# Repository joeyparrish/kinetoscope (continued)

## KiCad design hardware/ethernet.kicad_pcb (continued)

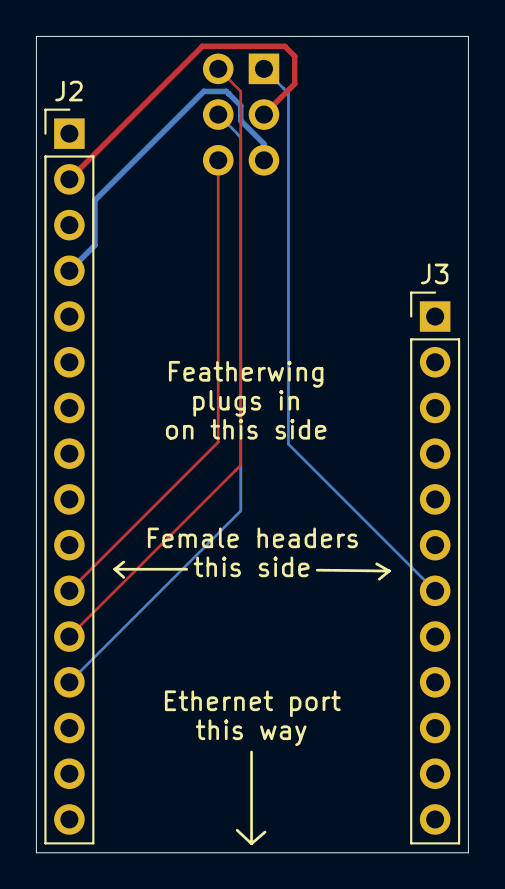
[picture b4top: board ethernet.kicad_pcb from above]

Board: 2 copper layers, 24.0 x 45.4 mm, 3 parts (1 on the bottom side), 6 nets.

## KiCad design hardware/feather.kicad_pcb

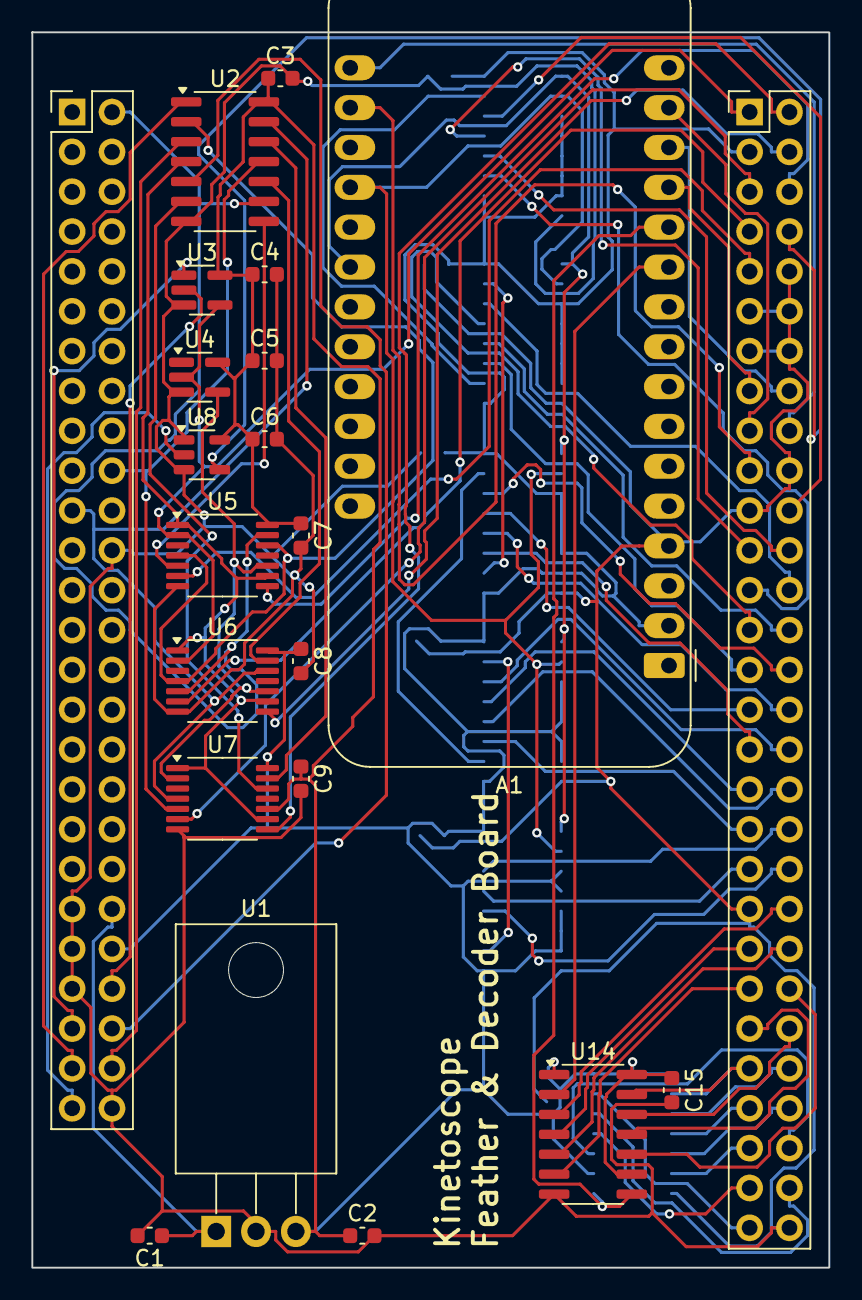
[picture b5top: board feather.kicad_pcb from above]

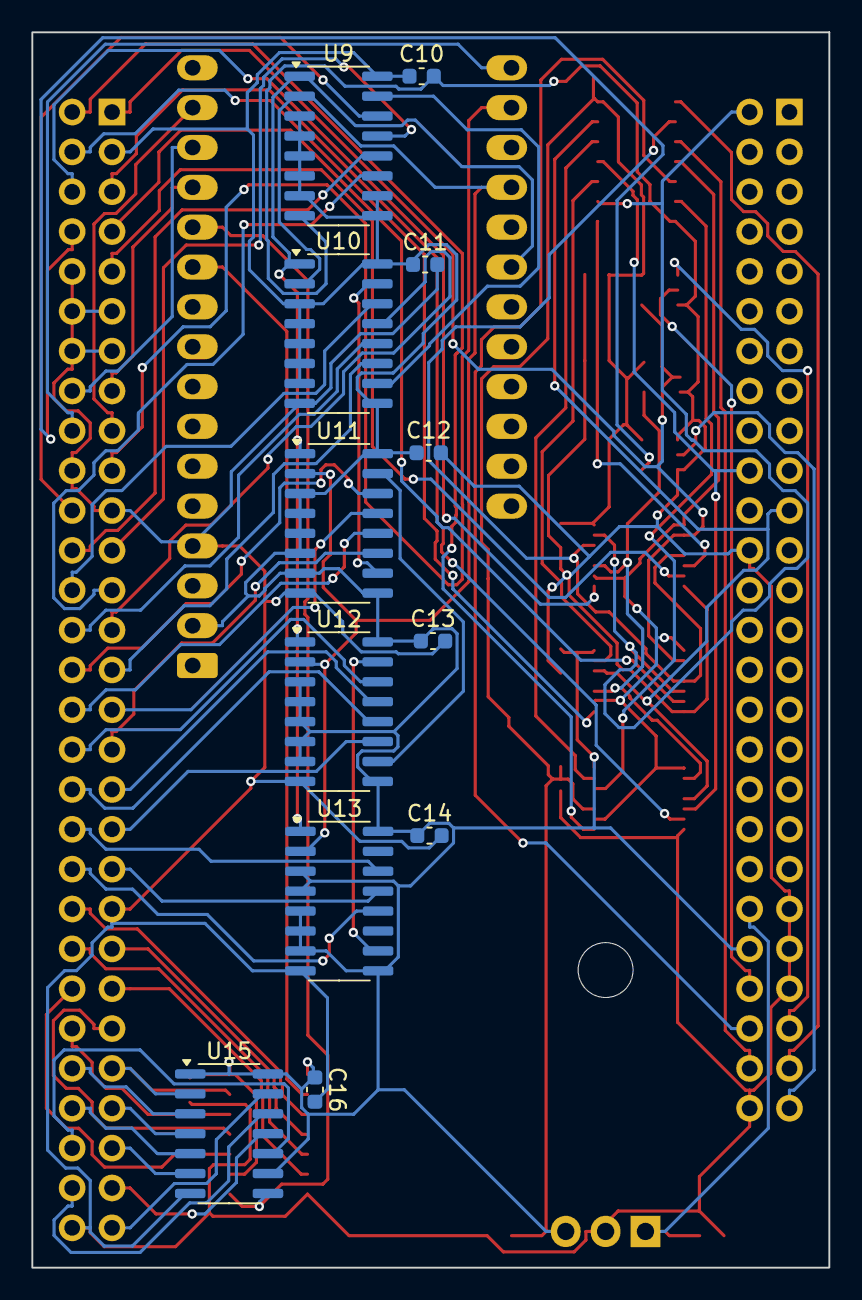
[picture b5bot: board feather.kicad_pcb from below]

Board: 2 copper layers, 50.8 x 78.7 mm, 33 parts (12 on the bottom side), 75 nets.

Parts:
A1: Adafruit_Feather
C1: 4.7uF; C_0603_1608Metric
C2: 1uF; C_0603_1608Metric
C3, C4, C5, C6, C7, C8, C9, C10, C11, C12, C13, C14, C15, C16: 22nF; C_0603_1608Metric
J1: kinetoscope-cart-header
U1: MCP1827S-3302E/AB; TO-220-3_Horizontal_TabDown
U2: MC74VHC04DR2G; SOIC-14_3.9x8.7mm_P1.27mm
U3: MC74VHC1G00DBVT1G; SC-74A-5_1.55x2.9mm_P0.95mm
U4: MC74VHC1G04DBVT1G; SC-74A-5_1.55x2.9mm_P0.95mm
U5, U6, U7: 74VHC20FT; TSSOP-14_4.4x5mm_P0.65mm
U8: SN74LV1T125DBVRG4; SOT-23-5
U9, U10, U11, U12, U13: SN74LV163ADR; SOIC-16_3.9x9.9mm_P1.27mm
U14, U15: 74LV164D,118; SOIC-14_3.9x8.7mm_P1.27mm

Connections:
/3V: A1.2 (3V3), C2.1, C3.1, C4.1, C5.1, C6.1, C7.1, C8.1, C9.1, C10.1, C11.1, C12.1, C13.1, C14.1, C15.1, C16.1, J1.44 (3V), J1.55 (~FLASH_WE), U1.3 (VO), U2.14 (VCC), U3.5 (VCC), U4.5 (VCC), U5.14 (VCC), U6.14 (VCC), U7.10, U7.14 (VCC), U8.5 (VCC), U9.3 (D0), U9.4 (D1), U9.5 (D2), U9.6 (D3), U9.7 (CEP), U9.9 (~PE), U9.10 (CET), U9.16 (VCC), U10.3 (D0), U10.4 (D1), U10.5 (D2), U10.6 (D3), U10.7 (CEP), U10.9 (~PE), U10.16 (VCC), U11.3 (D0), U11.4 (D1), U11.5 (D2), U11.6 (D3), U11.7 (CEP), U11.9 (~PE), U11.16 (VCC), U12.3 (D0), U12.4 (D1), U12.5 (D2), U12.6 (D3), U12.7 (CEP), U12.9 (~PE), U12.16 (VCC), U13.3 (D0), U13.4 (D1), U13.5 (D2), U13.6 (D3), U13.7 (CEP), U13.9 (~PE), U13.16 (VCC), U14.1 (DSA), U14.9 (~MR), U14.14 (VCC), U15.1 (DSA), U15.9 (~MR), U15.14 (VCC)
/5V: C1.1, J1.42 (5V), U1.1 (VI)
/GND: A1.4 (GND), C1.2, C2.2, C3.2, C4.2, C5.2, C6.2, C7.2, C8.2, C9.2, C10.2, C11.2, C12.2, C13.2, C14.2, C15.2, C16.2, J1.24 (GND), J1.41 (GND), J1.43 (GND), J1.45 (GND), J1.52 (GND), J1.62 (GND), J1.63 (GND), J1.64 (GND), J1.65 (GND), J1.66 (GND), J1.72 (GND), J1.73 (GND), J1.93 (GND), J1.110 (GND), U1.2 (ADJ), U2.7 (GND), U3.3 (GND), U4.3 (GND), U5.7 (GND), U6.7 (GND), U7.7 (GND), U8.1 (~OE), U8.3 (GND), U9.8 (GND), U10.8 (GND), U11.8 (GND), U12.8 (GND), U13.8 (GND), U14.7 (GND), U15.7 (GND)
/SCL: A1.18 (SCL/IO20), J1.71 (SCL)
/SDA: A1.17 (SDA/IO22), J1.70 (SDA)
/SRAM_DIS_1: A1.14 (RX/IO7), J1.68 (SRAM_DIS_1)
/SRAM_DIS_2: A1.15 (TX/IO8), J1.69 (SRAM_DIS_2)
/SRAM_D_CLK: A1.12 (MOSI/IO19), U14.8 (CP), U15.8 (CP)
/SRAM_D_IN0: J1.94 (SRAM_D_IN0), U14.3 (Q0)
/SRAM_D_IN1: J1.95 (SRAM_D_IN1), U14.4 (Q1)
/SRAM_D_IN2: J1.96 (SRAM_D_IN2), U14.5 (Q2)
/SRAM_D_IN3: J1.97 (SRAM_D_IN3), U14.6 (Q3)
/SRAM_D_IN4: J1.98 (SRAM_D_IN4), U14.10 (Q4)
/SRAM_D_IN5: J1.99 (SRAM_D_IN5), U14.11 (Q5)
/SRAM_D_IN6: J1.100 (SRAM_D_IN6), U14.12 (Q6)
/SRAM_D_IN7: J1.101 (SRAM_D_IN7), U14.13 (Q7), U15.2 (DSB)
/SRAM_D_IN8: J1.102 (SRAM_D_IN8), U15.3 (Q0)
/SRAM_D_IN9: J1.103 (SRAM_D_IN9), U15.4 (Q1)
/SRAM_D_IN10: J1.104 (SRAM_D_IN10), U15.5 (Q2)
/SRAM_D_IN11: J1.105 (SRAM_D_IN11), U15.6 (Q3)
/SRAM_D_IN12: J1.106 (SRAM_D_IN12), U15.10 (Q4)
/SRAM_D_IN13: J1.107 (SRAM_D_IN13), U15.11 (Q5)
/SRAM_D_IN14: J1.108 (SRAM_D_IN14), U15.12 (Q6)
/SRAM_D_IN15: J1.109 (SRAM_D_IN15), U15.13 (Q7)
/SRAM_D_NEXT: A1.11 (SCK/IO5), U14.2 (DSB)
/SRAM_W_A0: J1.74 (SRAM_W_A0), U9.14 (Q0)
/SRAM_W_A1: J1.75 (SRAM_W_A1), U9.13 (Q1)
/SRAM_W_A2: J1.76 (SRAM_W_A2), U9.12 (Q2)
/SRAM_W_A3: J1.77 (SRAM_W_A3), U9.11 (Q3)
/SRAM_W_A4: J1.78 (SRAM_W_A4), U10.14 (Q0)
/SRAM_W_A5: J1.79 (SRAM_W_A5), U10.13 (Q1)
/SRAM_W_A6: J1.80 (SRAM_W_A6), U10.12 (Q2)
/SRAM_W_A7: J1.81 (SRAM_W_A7), U10.11 (Q3)
/SRAM_W_A8: J1.82 (SRAM_W_A8), U11.14 (Q0)
/SRAM_W_A9: J1.83 (SRAM_W_A9), U11.13 (Q1)
/SRAM_W_A10: J1.84 (SRAM_W_A10), U11.12 (Q2)
/SRAM_W_A11: J1.85 (SRAM_W_A11), U11.11 (Q3)
/SRAM_W_A12: J1.86 (SRAM_W_A12), U12.14 (Q0)
/SRAM_W_A13: J1.87 (SRAM_W_A13), U12.13 (Q1)
/SRAM_W_A14: J1.88 (SRAM_W_A14), U12.12 (Q2)
/SRAM_W_A15: J1.89 (SRAM_W_A15), U12.11 (Q3)
/SRAM_W_A16: J1.90 (SRAM_W_A16), U13.14 (Q0)
/SRAM_W_A17: J1.91 (SRAM_W_A17), U13.13 (Q1)
/SRAM_W_A18: J1.92 (SRAM_W_A18), U13.12 (Q2)
/SRAM_W_A_CLK: A1.20 (ADC1_CH4/D32/IO32), U9.2 (CP), U10.2 (CP), U11.2 (CP), U12.2 (CP), U13.2 (CP)
/decoder-internal/READ: U4.4, U5.10, U6.10, U7.2
/decoder-internal/SEGA_A2: J1.2 (SEGA_A2), U2.9, U5.13, U6.5
/decoder-internal/SEGA_A20: J1.20 (SEGA_A20), U2.11, U7.5
/decoder-internal/SEGA_A21: J1.21 (SEGA_A21), U2.13, U6.12, U7.4
/decoder-internal/SEGA_AS: U2.4, U5.1, U5.9, U6.1, U6.9, U7.1, U7.9
/decoder-internal/SEGA_CE: U2.6, U7.12
/decoder-internal/SEGA_REGISTER: U2.2, U5.4, U5.12, U6.4
/decoder-internal/WRITE: J1.53 (~FLASH_OE), U3.4, U4.2, U5.2, U6.2
/decoder-internal/~FLASH_CE: J1.54 (~FLASH_CE), U7.8
/decoder-internal/~REG_WE: J1.61 (~REG_WE), U5.6
/decoder-internal/~RESET: J1.51 (~SEGA_RESET), U8.2 (A)
/decoder-internal/~SEGA_A2: U2.8, U5.5
/decoder-internal/~SEGA_A20: U2.10, U6.13
/decoder-internal/~SEGA_A21: U2.12, U7.13
/decoder-internal/~SEGA_AS: J1.50 (~SEGA_AS), U2.3
/decoder-internal/~SEGA_CE: J1.48 (~SEGA_CE), U2.5
/decoder-internal/~SEGA_REGISTER: J1.49 (~SEGA_REGISTER), U2.1
/decoder-internal/~SEGA_WE_LB: J1.46 (~SEGA_WE_LB), U3.2
/decoder-internal/~SEGA_WE_UB: J1.47 (~SEGA_WE_UB), U3.1
/decoder-internal/~SRAM_CE1: J1.56 (~SRAM_CE1), U6.8
/decoder-internal/~SRAM_CE2: J1.57 (~SRAM_CE2), U7.6
/decoder-internal/~SYNC_OE: J1.58 (~SYNC_OE), U5.8
/decoder-internal/~SYNC_SET: J1.59 (~SYNC_SET), U6.6
/~RESET_3V: J1.60 (~RESET_3V), U8.4 (Y)
/~SRAM_WE: A1.13 (MISO/IO21), J1.67 (~SRAM_WE)
/~SRAM_W_A_CLR: A1.22 (ADC1_CH5/D33/IO33), U9.1 (~MR), U10.1 (~MR), U11.1 (~MR), U12.1 (~MR), U13.1 (~MR)
unnamed: U9.15 (TC), U10.10 (CET)
unnamed: U10.15 (TC), U11.10 (CET)
unnamed: U11.15 (TC), U12.10 (CET)
unnamed: U12.15 (TC), U13.10 (CET)

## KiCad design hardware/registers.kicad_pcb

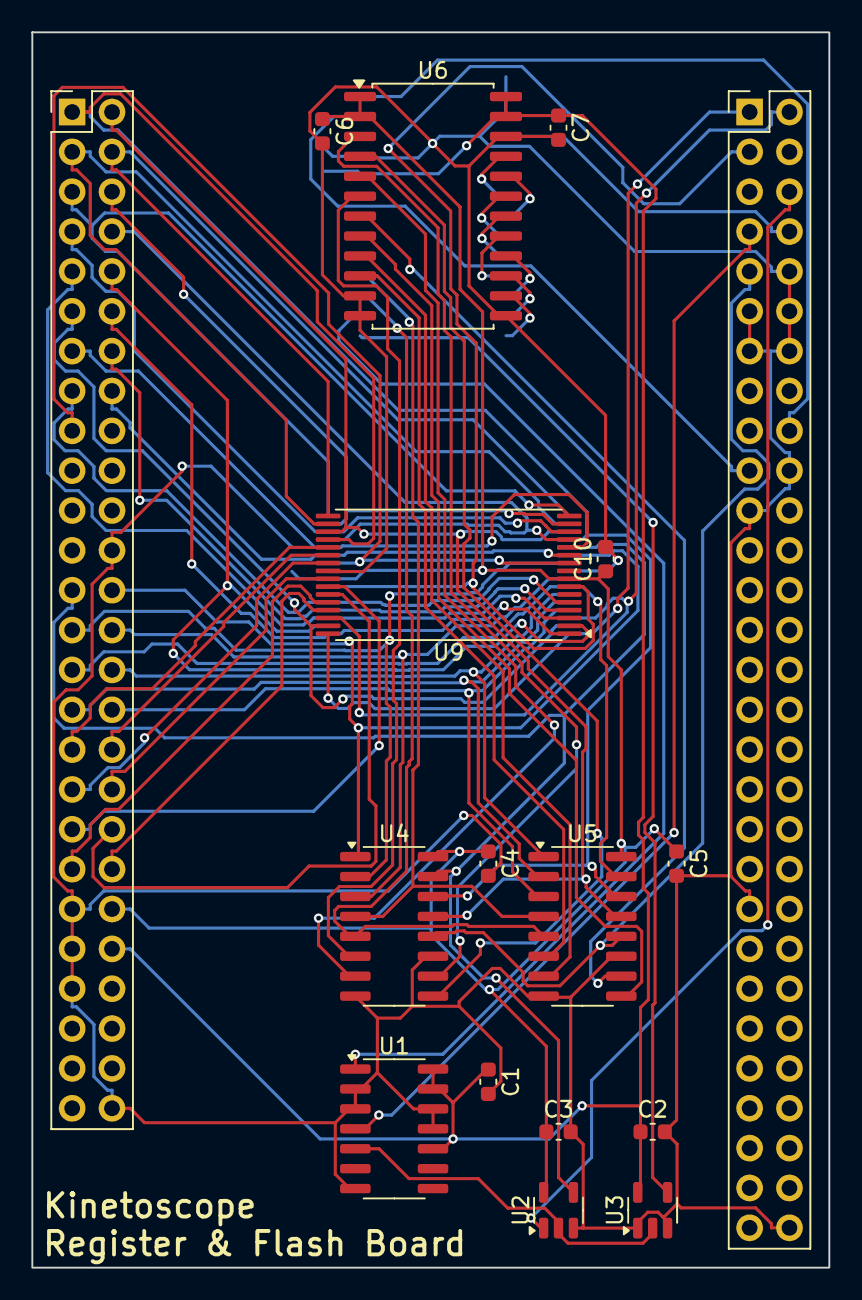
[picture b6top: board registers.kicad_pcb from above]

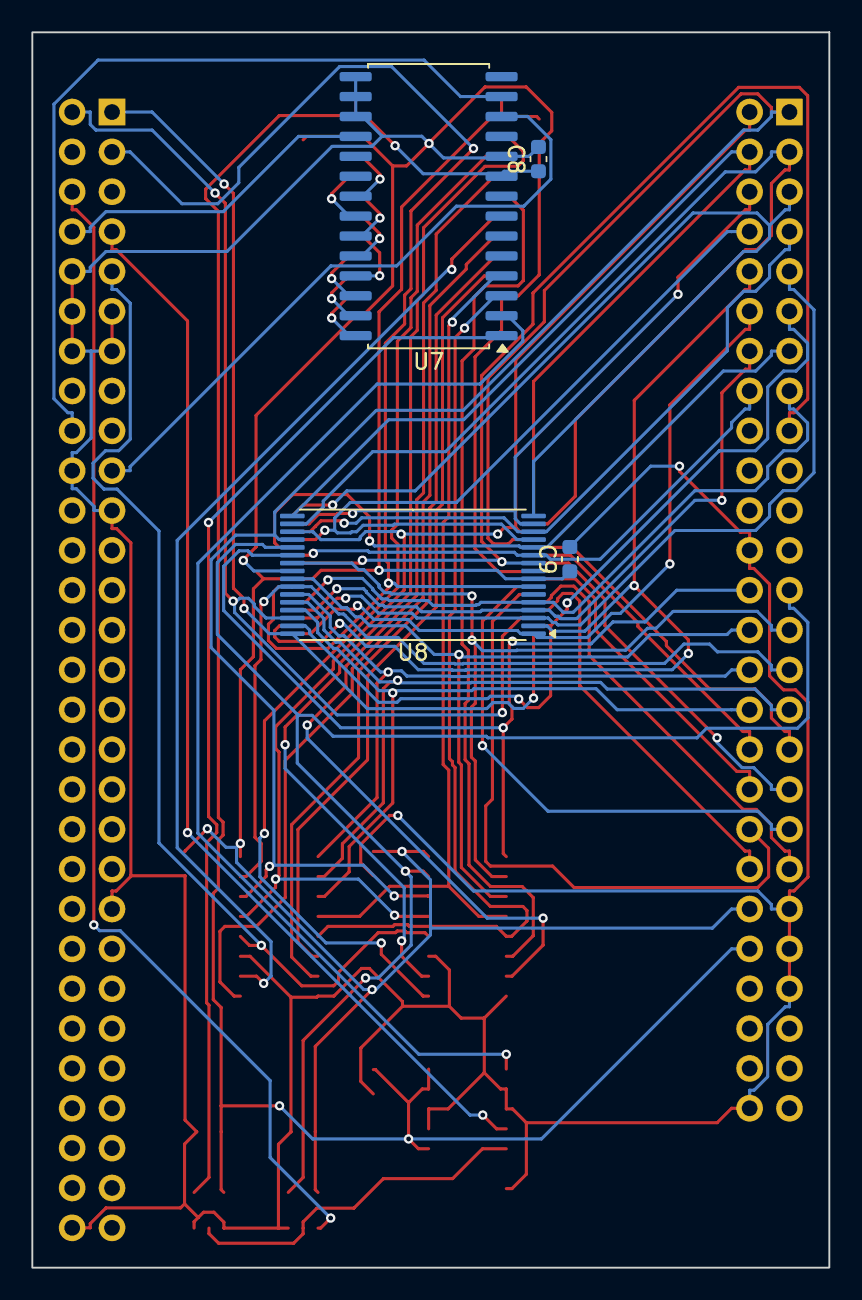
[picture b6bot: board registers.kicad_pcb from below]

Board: 2 copper layers, 50.8 x 78.7 mm, 20 parts (4 on the bottom side), 66 nets.

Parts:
C1, C2, C3, C4, C5, C6, C7, C8, C9, C10: 22nF; C_0603_1608Metric
J1: kinetoscope-cart-header
U1: 74AHC74D,118; SO-14_3.9x8.65mm_P1.27mm
U2, U3: SN74LV1T125DBVRG4; SOT-23-5
U4, U5: CD74HC670M96; SOIC-16_3.9x9.9mm_P1.27mm
U6: SN74LVC8T245DWRG4; SOIC-24W_7.5x15.4mm_P1.27mm
U7: MCP23017-E/SO; SOIC-28W_7.5x17.9mm_P1.27mm
U8, U9: SST39SF010A-55-4I-WHE; TSOP-I-32_14.4x8mm_P0.5mm

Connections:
/3V: C1.1, C2.1, C7.1, C8.1, J1.44 (3V), U1.10 (~S), U1.13 (~R), U1.14 (VCC), U3.5 (VCC), U6.23 (V_{CCB}), U6.24 (V_{CCB}), U7.9 (VDD)
/5V: C3.1, C4.1, C5.1, C6.1, C9.1, C10.1, J1.42 (5V), U2.5 (VCC), U4.16 (VCC), U5.16 (VCC), U6.1 (V_{CCA}), U6.2 (DIR), U8.8 (VCC), U9.8 (VCC)
/GND: C1.2, C2.2, C3.2, C4.2, C5.2, C6.2, C7.2, C8.2, C9.2, C10.2, J1.24 (GND), J1.41 (GND), J1.43 (GND), J1.45 (GND), J1.52 (GND), J1.62 (GND), J1.63 (GND), J1.64 (GND), J1.65 (GND), J1.66 (GND), J1.72 (GND), J1.73 (GND), J1.93 (GND), J1.110 (GND), U1.2 (D), U1.3 (C), U1.7 (GND), U1.11 (C), U1.12 (D), U2.3 (GND), U3.1 (~OE), U3.3 (GND), U4.8 (GND), U4.11 (~Er), U5.8 (GND), U5.11 (~Er), U6.11 (GND), U6.12 (GND), U6.13 (GND), U6.22 (~OE), U7.10 (VSS), U7.15 (A0), U7.16 (A1), U7.17 (A2), U8.24 (GND), U9.24 (GND)
/REG_R_A0: U4.5 (Ra), U5.5 (Ra), U7.3 (GPB2)
/REG_R_A1: U4.4 (Rb), U5.4 (Rb), U7.4 (GPB3)
/REG_R_D0: U6.21 (B1), U7.21 (GPA0)
/REG_R_D1: U6.20 (B2), U7.22 (GPA1)
/REG_R_D2: U6.19 (B3), U7.23 (GPA2)
/REG_R_D3: U6.18 (B4), U7.24 (GPA3)
/REG_R_D4: U6.17 (B5), U7.25 (GPA4)
/REG_R_D5: U6.16 (B6), U7.26 (GPA5)
/REG_R_D6: U6.15 (B7), U7.27 (GPA6)
/REG_R_D7: U6.14 (B8), U7.28 (GPA7)
/SCL: J1.71 (SCL), U7.12 (SCK)
/SDA: J1.70 (SDA), U7.13 (SDA)
/SEGA_A1: J1.1 (SEGA_A1), U4.14 (Wa), U5.14 (Wa), U8.20 (A0), U9.20 (A0)
/SEGA_A2: J1.2 (SEGA_A2), U4.13 (Wb), U5.13 (Wb), U8.19 (A1), U9.19 (A1)
/SEGA_A3: J1.3 (SEGA_A3), U8.18 (A2), U9.18 (A2)
/SEGA_A4: J1.4 (SEGA_A4), U8.17 (A3), U9.17 (A3)
/SEGA_A5: J1.5 (SEGA_A5), U8.16 (A4), U9.16 (A4)
/SEGA_A6: J1.6 (SEGA_A6), U8.15 (A5), U9.15 (A5)
/SEGA_A7: J1.7 (SEGA_A7), U8.14 (A6), U9.14 (A6)
/SEGA_A8: J1.8 (SEGA_A8), U8.13 (A7), U9.13 (A7)
/SEGA_A9: J1.9 (SEGA_A9), U8.3 (A8), U9.3 (A8)
/SEGA_A10: J1.10 (SEGA_A10), U8.2 (A9), U9.2 (A9)
/SEGA_A11: J1.11 (SEGA_A11), U8.31 (A10), U9.31 (A10)
/SEGA_A12: J1.12 (SEGA_A12), U8.1 (A11), U9.1 (A11)
/SEGA_A13: J1.13 (SEGA_A13), U8.12 (A12), U9.12 (A12)
/SEGA_A14: J1.14 (SEGA_A14), U8.4 (A13), U9.4 (A13)
/SEGA_A15: J1.15 (SEGA_A15), U8.5 (A14), U9.5 (A14)
/SEGA_A16: J1.16 (SEGA_A16), U8.11 (A15), U9.11 (A15)
/SEGA_A17: J1.17 (SEGA_A17), U8.10 (A16), U9.10 (A16)
/SEGA_D0: J1.25 (SEGA_D0), U2.4 (Y), U4.15 (D1), U8.21 (D0)
/SEGA_D1: J1.26 (SEGA_D1), U4.1 (D2), U8.22 (D1)
/SEGA_D2: J1.27 (SEGA_D2), U4.2 (D3), U8.23 (D2)
/SEGA_D3: J1.28 (SEGA_D3), U4.3 (D4), U8.25 (D3)
/SEGA_D4: J1.29 (SEGA_D4), U5.15 (D1), U8.26 (D4)
/SEGA_D5: J1.30 (SEGA_D5), U5.1 (D2), U8.27 (D5)
/SEGA_D6: J1.31 (SEGA_D6), U5.2 (D3), U8.28 (D6)
/SEGA_D7: J1.32 (SEGA_D7), U5.3 (D4), U8.29 (D7)
/SEGA_D8: J1.33 (SEGA_D8), U9.21 (D0)
/SEGA_D9: J1.34 (SEGA_D9), U9.22 (D1)
/SEGA_D10: J1.35 (SEGA_D10), U9.23 (D2)
/SEGA_D11: J1.36 (SEGA_D11), U9.25 (D3)
/SEGA_D12: J1.37 (SEGA_D12), U9.26 (D4)
/SEGA_D13: J1.38 (SEGA_D13), U9.27 (D5)
/SEGA_D14: J1.39 (SEGA_D14), U9.28 (D6)
/SEGA_D15: J1.40 (SEGA_D15), U9.29 (D7)
/TOKEN_3V: U3.4 (Y), U7.1 (GPB0)
/register-file-internal/D_MID0: U4.10 (Q1), U6.3 (A1)
/register-file-internal/D_MID1: U4.9 (Q2), U6.4 (A2)
/register-file-internal/D_MID2: U4.7 (Q3), U6.5 (A3)
/register-file-internal/D_MID3: U4.6 (Q4), U6.6 (A4)
/register-file-internal/D_MID4: U5.10 (Q1), U6.7 (A5)
/register-file-internal/D_MID5: U5.9 (Q2), U6.8 (A6)
/register-file-internal/D_MID6: U5.7 (Q3), U6.9 (A7)
/register-file-internal/D_MID7: U5.6 (Q4), U6.10 (A8)
/sync-token-internal/TOKEN_INT: U1.5 (Q), U2.2 (A), U3.2 (A)
/~FLASH_CE: J1.54 (~FLASH_CE), U8.30 (CE), U9.30 (CE)
/~FLASH_OE: J1.53 (~FLASH_OE), U8.32 (OE), U9.32 (OE)
/~FLASH_WE: J1.55 (~FLASH_WE), U8.7 (WE), U9.7 (WE)
/~REG_WE: J1.61 (~REG_WE), U4.12 (~Ew), U5.12 (~Ew)
/~RESET_3V: J1.60 (~RESET_3V), U7.18 (~RESET)
/~SYNC_CLR: U1.1 (~R), U7.2 (GPB1)
/~SYNC_OE: J1.58 (~SYNC_OE), U2.1 (~OE)
/~SYNC_SET: J1.59 (~SYNC_SET), U1.4 (~S)

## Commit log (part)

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2024-03-30 Fix build script running from inside project folder
2024-03-30 Remove kprintf unless DEBUG=1
2024-05-01 Ignore KiCad symbol and footprint backups
2024-05-03 Add register and sync token code to firmware
    So far I'm mostly just instrumenting the speed of various operations.
2024-05-03 Basic WiFi support, not doing much yet
2024-05-03 Reuse HTTP connections
    This does not seem to make a big difference in throughput
2024-05-16 Reorganize firmware to make it more reasonable to experiment
    Trying different microcontrollers and different network connections
2024-05-16 Not sure the pin-mode settings for RP2040 are working...
2024-05-17 Replace HTTP interface with a custom client that is MUCH faster
2024-05-17 Clean up fast-gpio
    No need for fast pin modes. These should stay constant.
    Also clean up in general and fix ESP32 pins > 31.
2024-05-22 Print crop settings during encoding
2024-06-15 Massively reorganize board designs
    Now planning to have most assembly done by JLCPCB, so trace sizes,
    part selections, etc. are set accordingly.
    New boards are:
    - cartridge interface & flash
    - microcontroller & registers
    - sram x2
2024-06-15 Add workflow to build firmware
2024-06-15 Add wired-wifi fallback and update measurements
2024-06-15 Fix ethernet chip-select and register address decoder
2024-06-16 Fix clearing error flag
2024-06-17 Update emulator to match latest hardware designs
2024-06-17 Add video to canned video list
2024-06-17 Cache KiCad packages to speed up hardware build workflow
2024-06-17 Complete release workflow
2024-06-17 Add note on patch licensing
2024-06-18 Add basic error-reporting
2024-06-21 Add notes on JLCPCB orders, add labels to debug connector
2024-06-21 Add ground fill on cart
2024-06-21 Bump cart date
2024-06-21 Clean up hardware release bundle
2024-06-28 Add workflow to update schematic PDFs automatically
2024-06-28 Debug PDF workflow
2024-06-30 Add notes on hardware prereqs
2024-06-30 Silence bogus warning in player about unaligned member access
2024-07-01 Add web demo
2024-07-02 Implement firmware command handling and second-core HTTP transfers
    - Avoid allocating strings in the heap (server and URL path names)
    - Allow HTTP transfers to be interrupted
    - Add stop command to streamer ROM
    - Add underflow handling to streamer ROM
    - Fix constness of internal interfaces
    - Add missing overview comments in headers
2024-07-04 Split player source from menu source
2024-07-05 Fix player state in streamer ROM
2024-07-05 Add canned inputs for simulated streamer hardware
2024-07-06 WIP: Redo emulator patches to stream with libcurl
    Before, everything was based on local files. Now, the emulator will
    use libcurl to stream from the same server (by default) that is used
    in the official firmware.
    This work is still incomplete. Only the video catalog is supported by
    this commit.
2024-07-06 Add relative_url field and catalog-creation tools
2024-07-07 Do not clobber older errors with newer ones
2024-07-08 Fold parser back into player, no longer used outside
2024-07-10 Do not extract URLs from SRAM in the emulator
    This avoids giving the emulator an ability the real hardware will not have, so that the firmware logic can be more similar to the emulator logic.
2024-07-11 Prep firmware for release
    - Fix bugs in 1-chunk playbacks
    - Disable debug & speed tests
    - Make EOF check safer
2024-07-11 Fix simulated streaming of embedded video
2024-07-11 Fix permissions of blastem in release zip
2024-07-11 Fix emulation to fetch in a thread
2024-07-11 Add catalog tool to encoder release
2024-07-14 Fix JLCPCB rotation automatically
    The lists in this script are incomplete, but work for the cart board
    and some of the microcontroller board.
2024-07-29 Reduce artifact retention time to 1 day
2024-07-29 Update schematic PDFs (#3)
    Generated by GitHub Actions
2024-07-29 Update out-of-date flash schematic comment
2024-07-30 Enable comparison of sound drivers via macros
    I haven't reached any incredible conclusions here. Sticking with XGM2
    until I find something better.
    There are others that purport to enable higher quality playback, but I
    can't figure out how to use them with SGDK and this player.
2024-07-31 Fix encoder failure on very short clips
    For example, Zoey Ann the Boxer.
2024-07-31 Fix emulator command delays
    The clock cycle counter was overflowing. This new one is time-based and uses 64 bits.
2024-08-10 Remove ethernet module, add pin header for Adafruit Ethernet featherwing instead
2024-08-13 Update schematic PDFs (#6)
    Generated by GitHub Actions
2024-08-16 Replace address counters with slightly larger versions that can be assembled more easily
2024-08-18 Add missing notes to the hardware README
2024-08-26 Fix microcontroller address decoders
    Verified on a breadboard
2024-08-31 Tweak port macros
    Probably makes no difference. But I feel better with all those extra parens.
2024-09-01 Simplify microcontroller board BOM
    Replace 74LV1T125 with 74LVC2G125, which simplifies the BOM by removing one special part.
2024-09-02 Add test pads to SRAM board
2024-09-03 Update schematic PDFs (#9)
    Generated by GitHub Actions
2024-09-03 Update schematic PDFs (#10)
    Generated by GitHub Actions
2024-09-03 Improve uC board assembly process, fix minor bug
    Changes to part numbers to better align with JLCPCB stock:
    - Replace 74LV164PW,118 / C179331 with SN74LV164APWR / C403720
    - Replace SN74LV163APWR / C2675453 with SN74LV161APWR / C2649404
    - Original had sync clear, but this is async clear, which is a bug
    fix!
    - Fix rotation of U8, U9, U13
2024-09-04 Fix new uC parts rotation
2024-09-04 Fix footprint for new SMD regulator
2024-09-04 Improve hardware docs
2024-09-05 Correct hardware docs
2024-09-13 WIP: build emulators for all three platforms
2024-09-15 Clear error flag after hardware echo check
2024-09-23 Rename sram_flush for clarity
2024-09-23 Move SRAM board references for clarity
2024-09-23 Make it easier to compile firmware out of the box without WiFi config
2024-09-24 Begin factoring out common logic between firmware, software, and emulators
2024-09-25 Add ethernet adapter board
2024-09-26 Increase spacing between tracks on Ethernet board
2024-09-30 Add two additional passes to the SRAM tests
2024-10-02 Fix error during encoding with --debug-audio
2024-10-03 Reroute SRAM board to match previous schematic changes
2024-10-03 Index and optional compression in video format
2024-10-03 Improve HTTP success rates in rare cases of slow starts
2024-10-03 Update header part numbers
    SSW pins are incompatible with other headers. SSQ should be better. (Yet to confirm.)
2024-10-03 Fix video catalog after playback in emulator
2024-10-03 Build BlastEm for Windows (mingw64)
2024-10-04 Fix macOS release artifacts
2024-10-05 Add notes for emulator downloads
2024-10-10 Improve HTTP client robustness and remove raw network tests
2024-10-11 Make march test errors easier to read
2024-10-12 Factor out video paths, add options for local hotspot server and for slow gpio
2024-10-13 Clean up march test failure messages
2024-10-13 Drop Samtec headers
    They do not connect well. I need more reliable stacking headers.
2024-10-13 Wait for serial before running speed tests
2024-10-14 Make the emulator patch a little more generic
2024-10-14 Add support for emulation in Genesis Plus GX and emscripten
    Also fixes bugs in preceding refactors
2024-10-15 Fix missing JS build artifacts
2024-10-15 Undo workflow hack
2024-10-15 Simplify buffer context cleanup in emulators
2024-10-16 Add network tests to the self-testing ROM
2024-10-16 Fix SRAM offset tracking in emulator
    Now handled entirely by write_sram()
2024-10-16 Tweak march test error formatting
2024-10-16 Stop playback on error
2024-10-16 Update schematic PDFs (#19)
    Generated by GitHub Actions
2024-10-16 Run build workflows whenever common code changes
2024-10-16 Add gesture support to the web demo
    This makes the web demo accessible on mobile devices without a dedicated keyboard.
2024-10-16 Add missing file for gesture support
2024-10-18 Add web demo instructions, clean up confusing inputs in streamer rom
2024-10-22 Disable multi-threaded route optimizer in freerouting
    It seems to be slower on the really difficult boards, and not much faster on the easy ones. It also has a tendency to cause clearance violations.
2024-11-23 Remove reset line from Sega to uC
    Also removes associated decoupler and pull-up resistor.
    Closes #20
2024-11-23 Tweak README wording
2024-12-03 Move presentation links
2025-08-01 Fix color quantization again
    It turns out that only 3 bits of data per channel are actually used, even though the in-memory format is 4 bits per channel. The low bit is ignored in each field, and only 512 colors are possible.
    All demo content will now be re-encoded to fix quality issues. The updates to the player folder here are in documentation only.
    See also joeyparrish/sega-slides#2
2025-08-04 Add missing Linux dep in emulator workflow
2025-09-17 Improve web demo landing page font sizes
2025-09-24 Migrate symbol and footprint tables into project-specific tables
2025-09-24 Move cart design into shareable subsheet
2025-09-24 Undo some global labels in the SRAM board
    The regex I used before was too broad. The new script is:
    ```perl
    #!/usr/bin/env perl -0777 -pi
    # The shebang above reads an entire file as a single input (0777), executes the
    # following transformations in a loop (-p) and overwrites the input file with
    # the results (-i).
2025-09-25 Layout for unified PCB
    Manual routing of ground vias, decoupling caps, and regulator
2025-09-28 Expand unified board by a LOT
    Hoping that this makes routing easier.
2025-09-28 First successful routing of a unified PCB
2025-09-28 Fix fab compat on macOS
2025-09-29 Fix concurrency issues between updating software and updating web demo
2025-09-29 Add kinetoscope cartridge startup sound
2025-10-02 Add encoder option to dump ffplay-playable file for analysis, comparison, debugging, etc.
2025-10-03 Reduce default scene-detection threshold
2025-10-04 Speed up encode by reducing I/O
    Use hard links instead of copying frames to scene folders
    Speeds up "All Good Things..." encode (92 minutes) on my workstation from ~0.95x to ~1.64x
2025-10-05 Speed up crop detection
    Only look at every 3rd keyframe. Not sure how much this actually
    helps, if at all.
2025-10-05 Fold tile encoding into final output step
    This removes a large chunk of disk IO by pipelining encoded tiles directly into the output file.
    Encoding "All Good Things..." (92 minutes) on my workstation now uses 1.7GB less temporary disk space.
2025-10-06 Fix backwards variable name and improve output for crop detection
2025-10-06 Fix unused rate detection in PCM driver
2025-10-07 Improve audio quality again
    Some content benefits more from noise filtering than others, and I am taking dithering on faith at this point.
2025-10-20 Add social media links
2025-10-26 Improve palette generation
    Use "diff" mode, which places more importance on the color fidelity of
    things that are moving, while allowing backgrounds to be less accurate.
2025-10-27 Be explicit about interlacing and shadow/highlight modes
